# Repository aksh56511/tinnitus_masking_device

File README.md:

# Tinnitus Masking Device

## Overview
This project presents the design and implementation of a PCB-based tinnitus masking device aimed at providing sound therapy for individuals experiencing tinnitus. The system generates controlled audio signals to reduce the perception of ringing in the ears.

## Features
- Compact and portable PCB design  
- Audio signal generation for tinnitus masking  
- Low-power operation  
- Simple and efficient circuit architecture  

## Hardware Design
The circuit was designed using KiCad, including schematic capture and PCB layout. The design ensures reliable signal generation and efficient power usage.

## Design Files
- Schematic (`.kicad_sch`)
- PCB Layout (`.kicad_pcb`)
- Project File (`.kicad_pro`)

## Images

### PCB Layout

### Schematic

### 3D View

## Applications
- Tinnitus sound therapy  
- Assistive biomedical devices  
- Low-cost healthcare electronics  

## Future Improvements
- Adjustable frequency range  
- Integration with microcontroller for adaptive control  
- Miniaturization for wearable applications  

## Author
Akshatha Pai

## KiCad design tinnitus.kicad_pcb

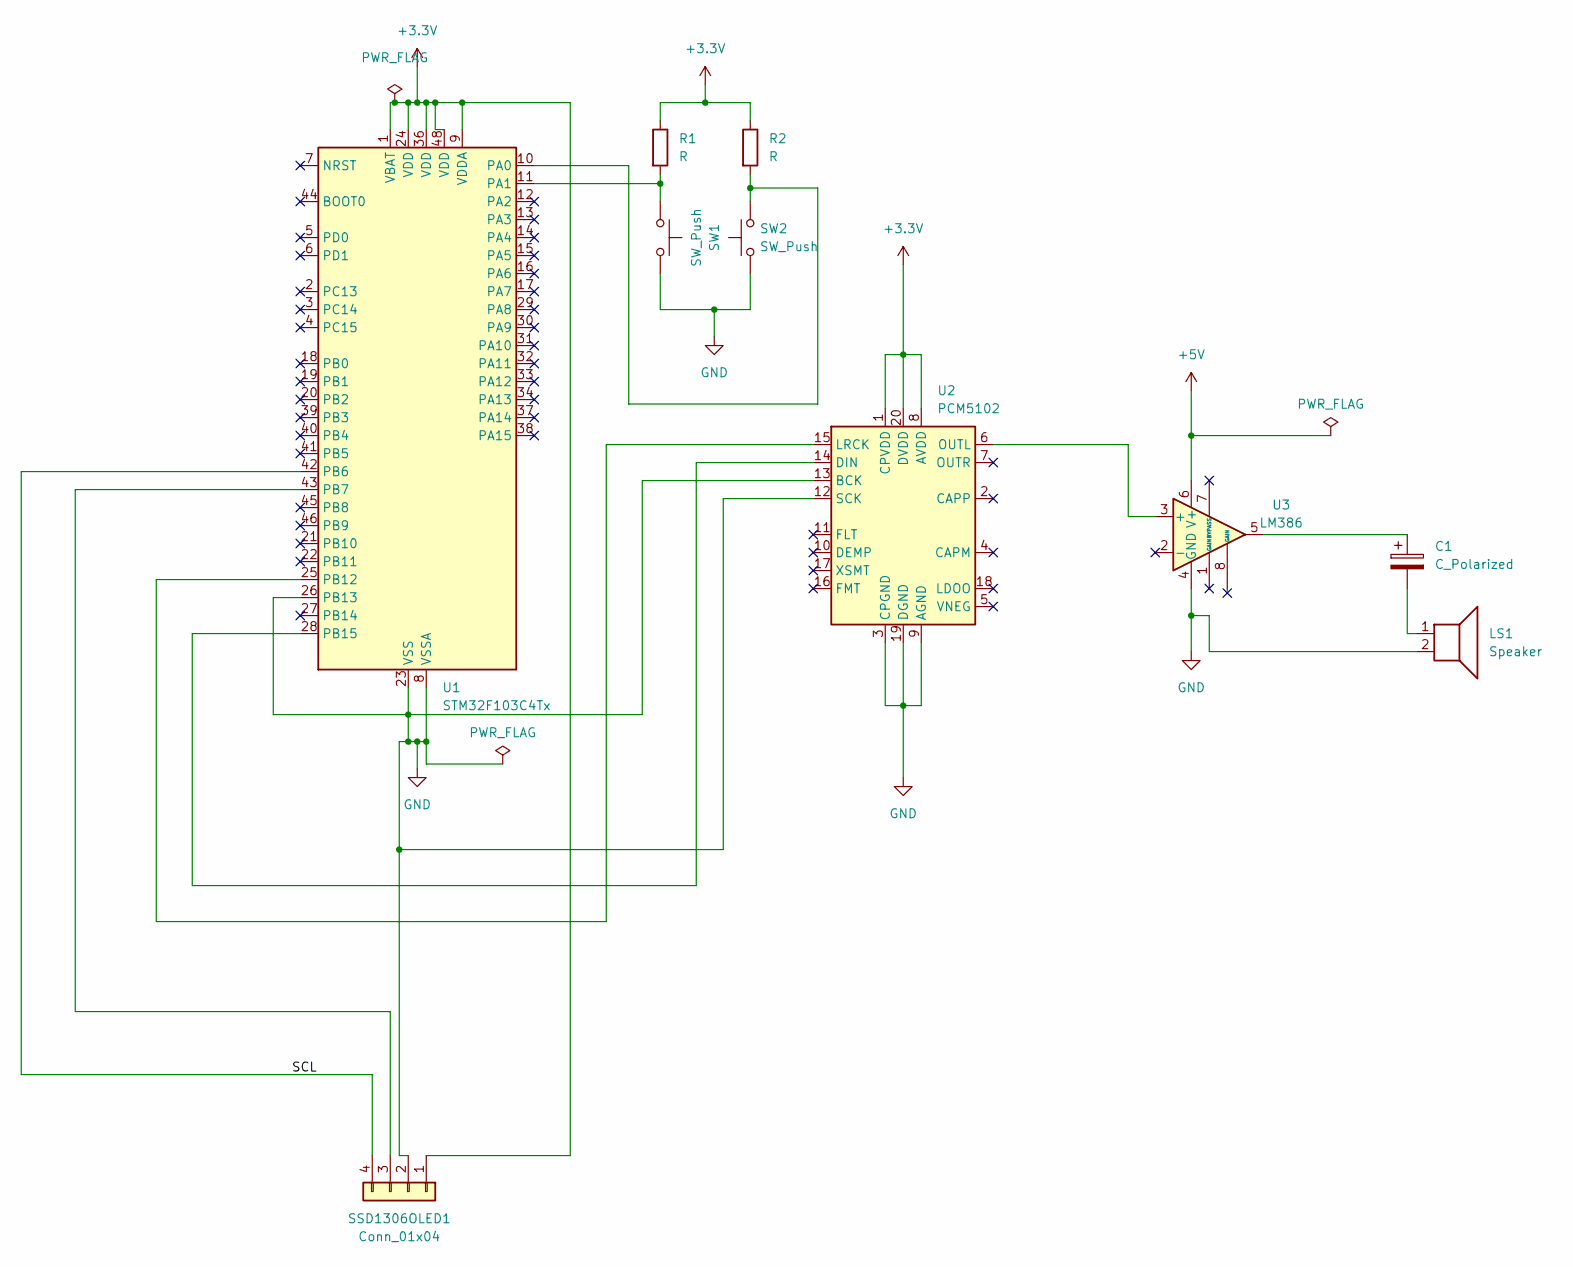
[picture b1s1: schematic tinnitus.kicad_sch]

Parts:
C1: C_Polarized; CP_Radial_D5.0mm_P2.00mm
LS1: Speaker; PinHeader_1x02_P2.54mm_Vertical
R1, R2: R; R_Axial_DIN0207_L6.3mm_D2.5mm_P7.62mm_Horizontal
SSD1306OLED1: Conn_01x04; PinHeader_1x04_P2.54mm_Vertical
SW1, SW2: SW_Push; SW_PUSH_6mm
U1: STM32F103C4Tx; LQFP-48_7x7mm_P0.5mm
U2: PCM5102; TSSOP-20_4.4x6.5mm_P0.65mm
U3: LM386; DIP-8_W7.62mm

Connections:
+3.3V: R1.1, R2.1, SSD1306OLED1.1, U1.1 (VBAT), U1.9 (VDDA), U1.24 (VDD), U1.36 (VDD), U1.48 (VDD), U2.1 (CPVDD), U2.8 (AVDD), U2.20 (DVDD)
+5V: U3.6 (V+)
/SCL: SSD1306OLED1.4, U1.42 (PB6)
GND: LS1.2, SSD1306OLED1.2, SW1.2, SW2.1, U1.8 (VSSA), U1.23 (VSS), U1.26 (PB13), U1.35 (VSS), U1.47 (VSS), U2.3 (CPGND), U2.9 (AGND), U2.12 (SCK), U2.13 (BCK), U2.19 (DGND), U3.4 (GND)
unnamed: C1.1, U3.5
unnamed: C1.2, LS1.1
unnamed: SSD1306OLED1.3, U1.43 (PB7)
unnamed: R2.2, SW2.2, U1.10 (PA0)
unnamed: R1.2, SW1.1, U1.11 (PA1)
unnamed: U1.25 (PB12), U2.15 (LRCK)
unnamed: U1.28 (PB15), U2.14 (DIN)
unnamed: U2.6 (OUTL), U3.3 (+)

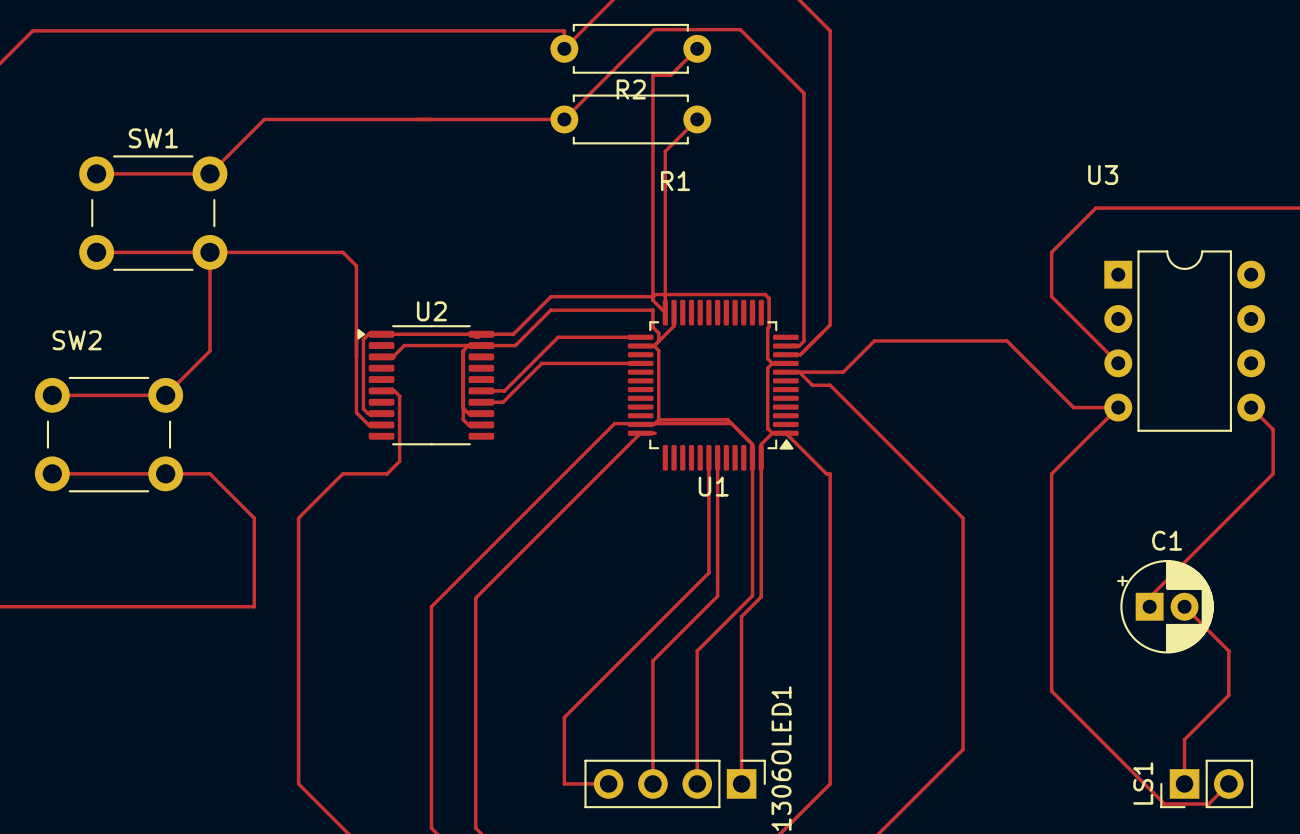
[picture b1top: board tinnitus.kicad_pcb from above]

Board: 2 copper layers, 10 parts (0 on the bottom side), 11 nets.

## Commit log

2026-05-01 Add initial project description for tinnitus masking device
2026-05-01 Enhance README with project details and features
    Expanded README to include project overview, features, hardware design, design files, images, applications, future improvements, and author information.
